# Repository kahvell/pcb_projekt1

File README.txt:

Projekt nr 1 płytki PCB w EAGLE 6.

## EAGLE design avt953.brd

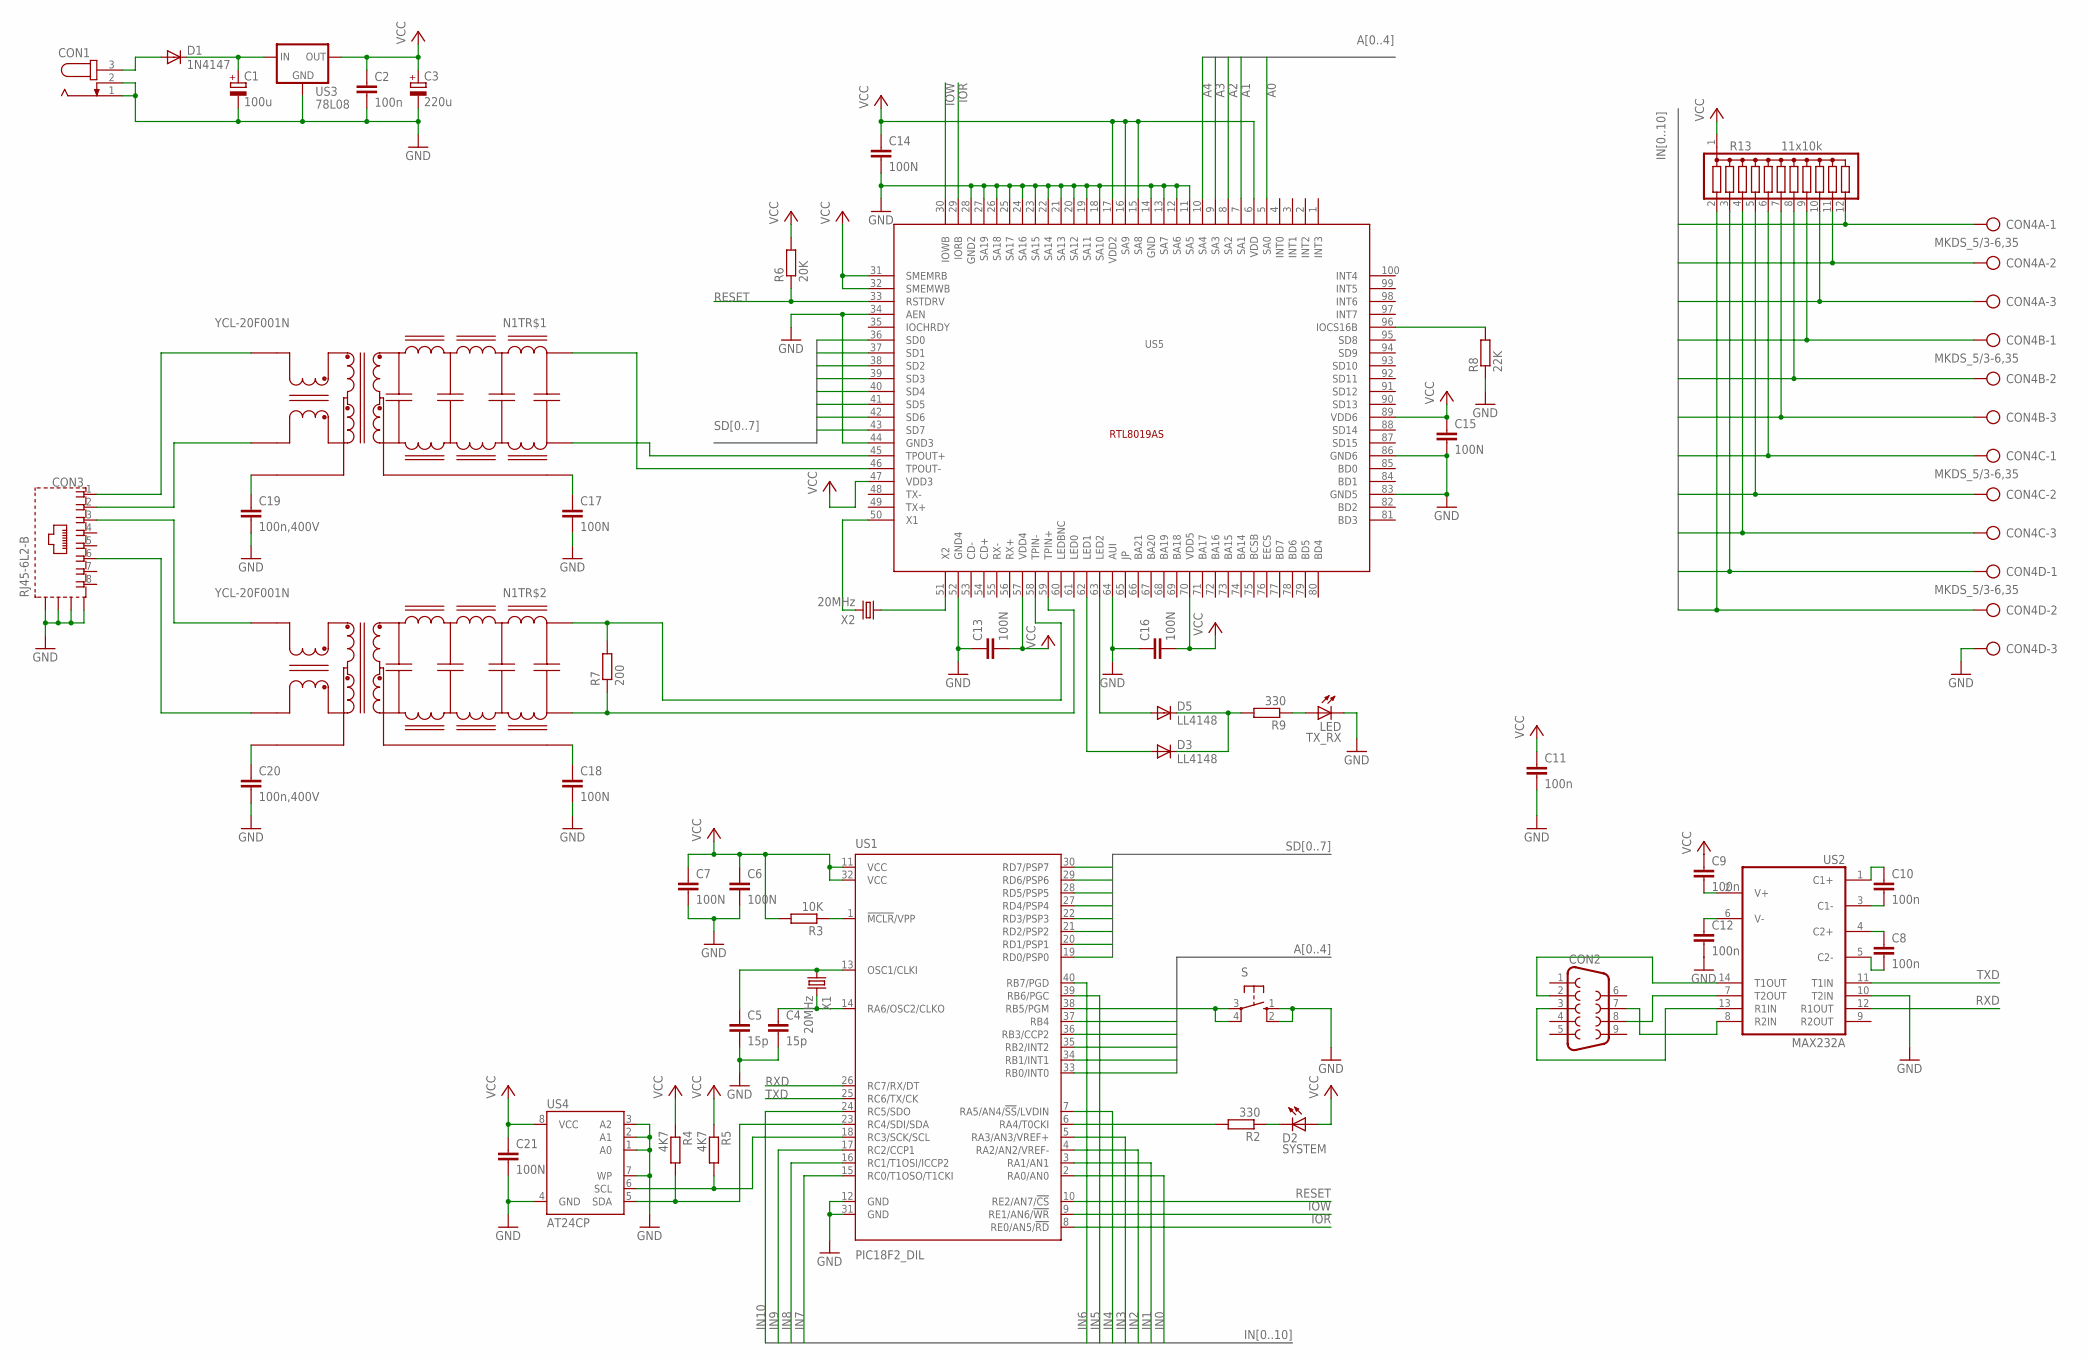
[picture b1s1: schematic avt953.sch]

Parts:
C1: 100u; TT2D5
C2, C8, C9, C10, C11, C12: 100n; C1206K
C3: 220u; TT2D5
C4, C5: 15p; C1206K
C6, C7, C13, C14, C15, C16, C17, C18, C21: 100N; C1206K
C19, C20: 100n,400V; C075-032X103
CON1: JACK-PLUG0; SPC4077
CON2: F09HP
CON3: RJ45-6L2-B; RJ45-SHIELD2
CON4A, CON4B, CON4C, CON4D: MKDS_5/3-6,35; MKDS_5/3-635
D1: 1N4147; DO35-10
D2: SYSTEM; LED5MM
D3, D5: LL4148; SOD-123_MINI-SMA
LED: TX_RX; LED5MM
N1: YCL-20F001N; DIP
R2, R9: 330; M3216
R3: 10K; M3216
R4, R5: 4K7; M3216
R6: 20K; M3216
R7: 200; M3216
R8: 22K; M3216
R13: 11x10k; SIL12
S: 10-XX; B3F-10XX
US1: PIC18F2_DIL; DIL40
US2: MAX232A; SO16L
US3: 78L08; 78XXL
US4: AT24CP; DIL08
US5: RTL8019AS
X1, X2: 20MHz; HC49/S

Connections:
A0: US1.33 (RB0/INT0), US5.5 (SA0)
A1: US1.34 (RB1/INT1), US5.7 (SA1)
A2: US1.35 (RB2/INT2), US5.8 (SA2)
A3: US1.36 (RB3/CCP2), US5.9 (SA3)
A4: US1.37 (RB4), US5.10 (SA4)
GND: C1.-, C2.2, C3.-, C4.2, C5.2, C6.2, C7.2, C11.2, C12.2, C13.1, C14.2, C15.2, C16.1, C17.2, C18.2, C19.2, C20.2, C21.2, CON1.1, CON1.2, CON2.5, CON3.S1 (S), CON3.S2 (S), CON3.S3 (S), CON3.S4 (S), CON4D.3, LED.K (C), R8.1, S.1 (S), S.2 (S1), US1.12 (GND), US1.31 (GND), US2.10 (T2IN), US2.15 (GND), US3.GND, US4.1 (A0), US4.2 (A1), US4.3 (A2), US4.4 (GND), US4.7 (WP), US5.11 (SA5), US5.12 (SA6), US5.13 (SA7), US5.14 (GND), US5.18 (SA10), US5.19 (SA11), US5.20 (SA12), US5.21 (SA13), US5.22 (SA14), US5.23 (SA15), US5.24 (SA16), US5.25 (SA17), US5.26 (SA18), US5.27 (SA19), US5.28 (GND2), US5.34 (AEN), US5.44 (GND3), US5.52 (GND4), US5.64 (AUI), US5.83 (GND5), US5.86 (GND6)
IN0: CON4A.1, R13.12, US1.2 (RA0/AN0)
IN1: CON4A.2, R13.11, US1.3 (RA1/AN1)
IN2: CON4A.3, R13.10, US1.4 (RA2/AN2/VREF-)
IN3: CON4B.1, R13.9, US1.5 (RA3/AN3/VREF+)
IN4: CON4B.2, R13.8, US1.7 (RA5/AN4/!SS!/LVDIN)
IN5: CON4B.3, R13.7, US1.39 (RB6/PGC)
IN6: CON4C.1, R13.6, US1.40 (RB7/PGD)
IN7: CON4C.2, R13.5, US1.15 (RC0/T1OSO/T1CKI)
IN8: CON4C.3, R13.4, US1.16 (RC1/T1OSI/ICCP2)
IN9: CON4D.1, R13.3, US1.17 (RC2/CCP1)
IN10: CON4D.2, R13.2, US1.24 (RC5/SDO)
IOR: US1.8 (RE0/AN5/!RD), US5.29 (IORB)
IOW: US1.9 (RE1/AN6/!WR), US5.30 (IOWB)
unnamed: C9.2, US2.2 (V+)
unnamed: C12.1, US2.6 (V-)
unnamed: C10.2, US2.3 (C1-)
unnamed: C10.1, US2.1 (C1+)
unnamed: C8.1, US2.4 (C2+)
unnamed: C8.2, US2.5 (C2-)
unnamed: CON2.2, US2.14 (T1OUT)
unnamed: CON2.8, US2.7 (T2OUT)
unnamed: CON2.3, US2.13 (R1IN)
unnamed: CON2.7, US2.8 (R2IN)
unnamed: CON1.3, D1.A
unnamed: C1.+, D1.C, US3.IN
unnamed: CON3.1, N1.P$16
unnamed: CON3.2, N1.P$14
unnamed: CON3.3, N1.P$11
unnamed: CON3.6, N1.P$9
unnamed: C19.1, N1.P$15
unnamed: C20.1, N1.P$10
unnamed: C18.1, N1.P$7
unnamed: C17.1, N1.P$2
unnamed: N1.P$3, US5.45 (TPOUT+)
unnamed: N1.P$8, R7.1, US5.59 (TPIN+)
unnamed: N1.P$1, US5.46 (TPOUT-)
unnamed: US5.50 (X1), X2.2
unnamed: N1.P$6, R7.2, US5.58 (TPIN-)
unnamed: D3.A, US5.62 (LED1)
unnamed: R8.2, US5.96 (IOCS16B)
unnamed: US5.51 (X2), X2.1
unnamed: D5.A, US5.63 (LED2)
unnamed: D3.C, D5.C, R9.2
unnamed: LED.A, R9.1
unnamed: C5.1, US1.13 (OSC1/CLKI), X1.1
unnamed: C4.1, US1.14 (RA6/OSC2/CLKO), X1.2
unnamed: R4.2, US1.23 (RC4/SDI/SDA), US4.5 (SDA)
unnamed: R3.1, US1.1 (!MCLR!/VPP)
unnamed: R2.2, US1.6 (RA4/T0CKI)
unnamed: R5.2, US1.18 (RC3/SCK/SCL), US4.6 (SCL)
unnamed: D2.K (C), R2.1
unnamed: S.3, S.4 (P1), US1.38 (RB5/PGM)
RESET: R6.1, US1.10 (RE2/AN7/!CS), US5.33 (RSTDRV)
RXD: US1.26 (RC7/RX/DT), US2.12 (R1OUT)
SD0: US1.19 (RD0/PSP0), US5.36 (SD0)
SD1: US1.20 (RD1/PSP1), US5.37 (SD1)
SD2: US1.21 (RD2/PSP2), US5.38 (SD2)
SD3: US1.22 (RD3/PSP3), US5.39 (SD3)
SD4: US1.27 (RD4/PSP4), US5.40 (SD4)
SD5: US1.28 (RD5/PSP5), US5.41 (SD5)
SD6: US1.29 (RD6/PSP6), US5.42 (SD6)
SD7: US1.30 (RD7/PSP7), US5.43 (SD7)
TXD: US1.25 (RC6/TX/CK), US2.11 (T1IN)
VCC: C2.1, C3.+, C6.1, C7.1, C9.1, C11.1, C13.2, C14.1, C15.1, C16.2, C21.1, D2.A, R3.2, R4.1, R5.1, R6.2, R13.1, US1.11 (VCC), US1.32 (VCC), US2.16 (VCC), US3.OUT, US4.8 (VCC), US5.6 (VDD), US5.15 (SA8), US5.16 (SA9), US5.17 (VDD2), US5.31 (SMEMRB), US5.32 (SMEMWB), US5.47 (VDD3), US5.57 (VDD4), US5.70 (VDD5), US5.89 (VDD6)

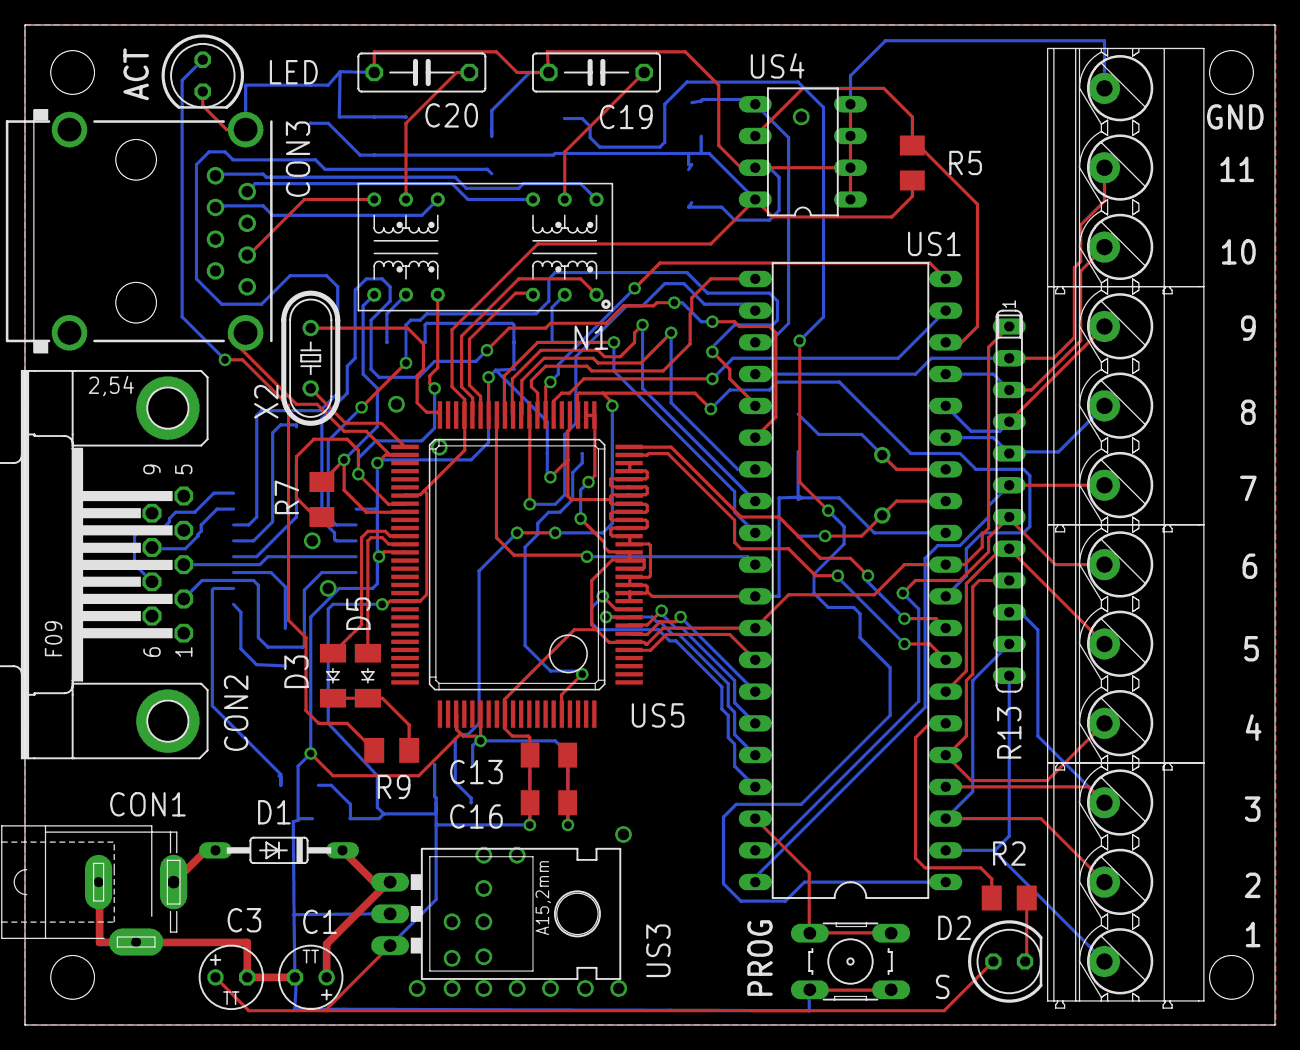
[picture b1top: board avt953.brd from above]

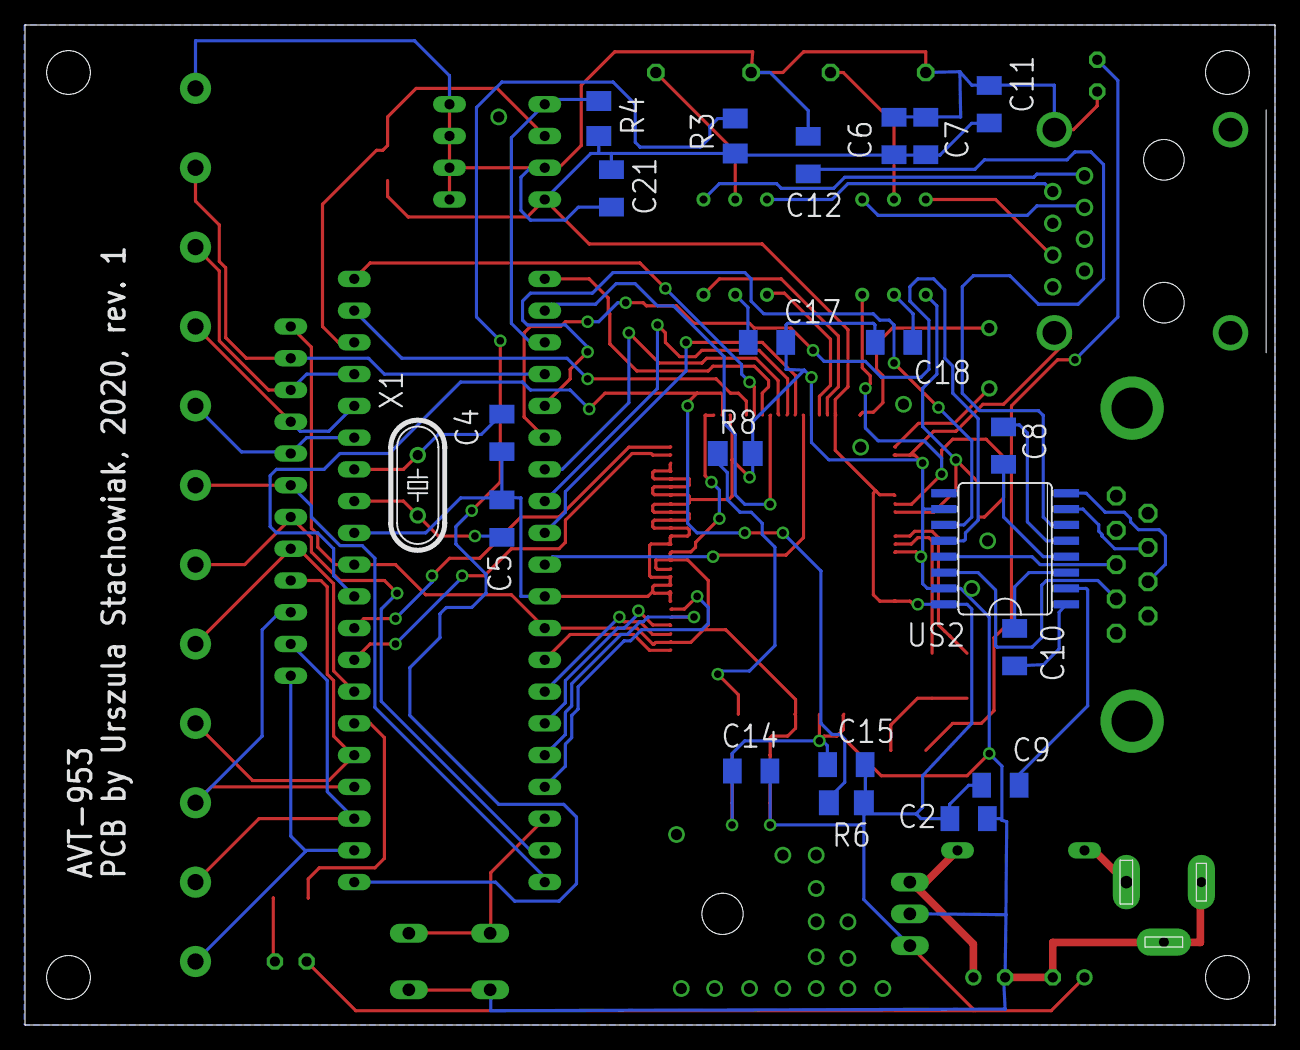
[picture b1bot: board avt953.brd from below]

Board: 2 copper layers, 100.0 x 80.0 mm, 51 parts (21 on the bottom side), 70 nets.

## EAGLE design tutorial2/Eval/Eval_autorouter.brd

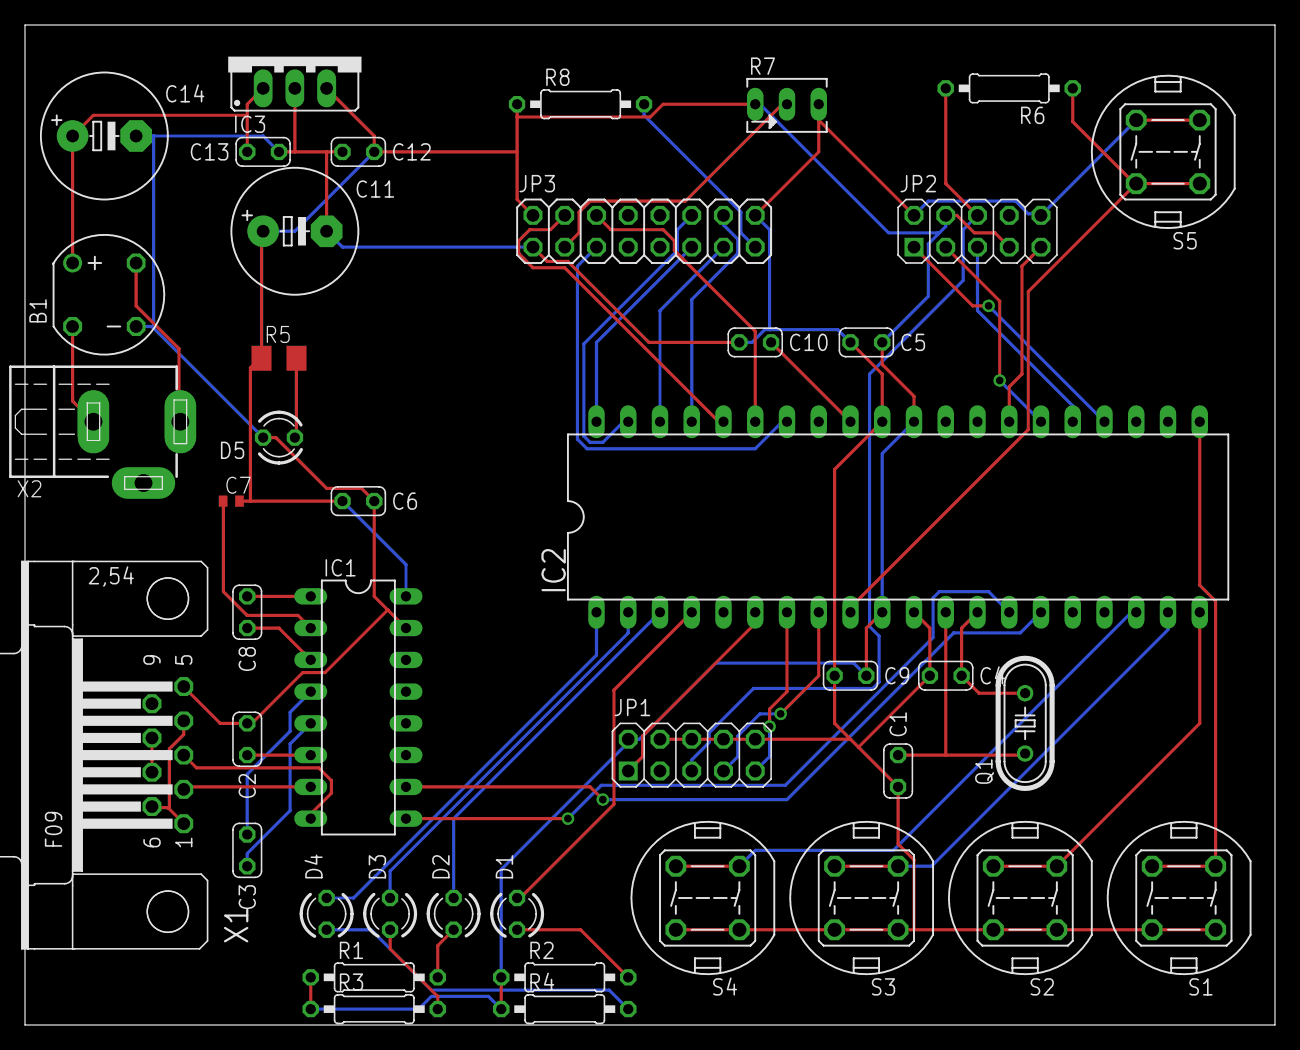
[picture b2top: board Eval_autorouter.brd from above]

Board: 2 copper layers, 100.0 x 80.0 mm, 42 parts (0 on the bottom side), 51 nets.

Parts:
B1: RB1A
C1, C4: 33pF; C025-024X044
C2, C3, C5, C6, C8, C9, C10, C12, C13: 100nF; C025-024X044
C7: 100nF; C0402
C11, C14: 470u/25V; E5-10,5
D1, D2, D3, D4: Red; LED3MM
D5: Green; LED3MM
IC1: MAX232; DIL16
IC2: MEGA16-P; DIL40
IC3: 7805; 78XXS
JP1, JP2: 2x5; 2X05
JP3: 2x8; 2X08
Q1: 16MHz; HC49/S
R1, R2, R3, R4: 220R; 0207/10@1
R5: 220R; M1206
R6: 510R; 0207/10@1
R7: 10k; B64Y
R8: 22R; 0207/10@1
S1, S2, S3, S4, S5: DTE6
X1: F09H
X2: NEB21R

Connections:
+5V: C5.2, C6.1, C7.2, C9.2, C11.+, C12.2, IC1.16, IC2.10, IC2.30, IC3.OUT, JP1.2, JP2.4, JP2.7, JP3.2, R1.1, R2.1, R3.1, R4.1, R5.1, R7.E, R8.1
/RESET: IC2.9, R6.1, S5.1, S5.2
/RESET_ISP: JP1.5, JP2.6, R6.2
DB4: IC2.40, JP3.11
DB5: IC2.39, JP3.12
DB6: IC2.38, JP3.13
DB7: IC2.37, JP3.14
E: IC2.35, JP3.6
GND: B1.-, C1.1, C2.1, C4.1, C5.1, C6.2, C9.1, C10.1, C11.-, C12.1, C13.1, C14.-, D5.K, IC1.15, IC2.11, IC2.31, IC3.GND, JP1.4, JP1.6, JP1.8, JP1.10, JP2.2, JP2.10, JP3.1, JP3.16, R7.A, S1.1, S1.2, S2.1, S2.2, S3.1, S3.2, S4.1, S4.2, S5.3, S5.4, X1.5
LED0: D4.K, IC2.1
LED1: D3.K, IC2.2
LED2: D2.K, IC2.3
LED3: D1.K, IC2.4
LED-A: JP3.15, R8.2
MISO: IC2.7, JP1.9
MOSI: IC2.6, JP1.1
unnamed: D4.A, R4.2
unnamed: D3.A, R3.2
unnamed: D2.A, R1.2
unnamed: D1.A, R2.2
unnamed: C10.2, IC2.32
unnamed: C2.2, IC1.6
unnamed: C7.1, IC1.2
unnamed: C3.2, IC1.5
unnamed: C3.1, IC1.4
unnamed: C8.2, IC1.3
unnamed: C8.1, IC1.1
unnamed: C4.2, IC2.13, Q1.2
unnamed: C1.2, IC2.12, Q1.1
unnamed: X1.1, X1.4, X1.6
unnamed: D5.A, R5.2
unnamed: B1.AC2, X2.-
unnamed: X1.7, X1.8
unnamed: B1.AC1, X2.+
unnamed: B1.+, C13.2, C14.+, IC3.IN
R/W: IC2.34, JP3.5
RS: IC2.36, JP3.4
RS232-RX0: IC1.8, X1.3
RS232-TX0: IC1.7, X1.2
RXD0: IC1.9, IC2.14
SCK: IC2.8, JP1.7
SW4: IC2.18, S4.3, S4.4
SW5: IC2.19, S3.3, S3.4
SW6: IC2.20, S2.3, S2.4
SW7: IC2.21, S1.3, S1.4
TCK: IC2.24, JP2.1
TDI: IC2.27, JP2.9
TDO: IC2.26, JP2.3
TMS: IC2.25, JP2.5
TXD0: IC1.10, IC2.15
V0: JP3.3, R7.S

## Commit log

2020-04-21 Dodano plik projektu EAGLE i specyfikację płytki do zaprojektowania.
2020-04-23 Dodano dokumentację transformatora Ethernet.
2020-04-23 Dodano dokumentację mikrokontrolera PIC.
2020-04-23 Dodano bibliotekę z układem scalonym - kontrolerem Ethernet.
2020-04-23 Dodano oryginalną biblotekę microchip.lbr z EAGLE 6.6.0.
2020-04-23 Do biblioteki microchip.lbr dodano device PIC18F452 w obudowie DIL40.
2020-04-23 Umieszczono co bardziej nietypowe komponenty na schemacie i dobrano footprinty.
2020-04-23 Dodano datasheety układów scalonych.
2020-04-23 Dodano plik .gitignore dla archiwalnych wersji płytek, schematów i bibliotek.
2020-04-23 Dopasowano nazwy na schemacie do wytycznych.
2020-04-28 Dodano firmware mikrokontrolera z projektu, zaciągnięty z archiwum Elektroniki Praktycznej.
2020-04-29 Dodano bibliotekę z transformatorem ethernetowym 10BASE-T YCL-20F001N. Umieszczono to trafo na schemacie.
2020-04-30 Zaprojektowano kompletny schemat układu.Przygotowano na jego podstawie pusty projekt płytki PCB i rozmieszczono co większe elementy.
2020-05-01 Przeprowadzono test ERC na schemacie i poprawiono zaraportowane błędy.
2020-05-01 Wstępnie rozmieszczono wszystkie elementy na projekcie płytki PCB.
2020-05-01 Dodano otwory montażowe M3 w rogach płytki.
2020-05-01 Przepuszczono płytkę przez autorouter z wynikiem 72,6%.
2020-05-01 Cofnięcie autoroutera. Zmiana kolejności wyprowadzeń IN (bo pin GND) nie był zewnętrznym pinem.
2020-05-01 Przepuszczono płytkę jeszcze raz przez autorouter, rozluźniając kryteria dodania przelotek i zmiany kierunku ścieżek. Brzydko wyszło, ale wynik 100%.
2020-05-01 Poprawki po autorouterze. Usunięto sporo przelotek, a pozostałe oddalono od siebie.
2020-05-01 Dodano szablon testu DRC za https://www.allpcb.com/standard_pcb_manufacturing_capability.html. Poddano płytkę testowi i poprawiono drobne błędy.
2020-05-01 Nie było połączenia z masą w konektorze RS232.
2020-05-01 Oblano warstwy top i bottom masą. Uzupełniono przelotki.
2020-05-01 Poprawiono i uzupełniono opisy w silkscreenie warstwy top.
2020-05-01 Poprawiono krytyczny błąd. Trzy elementy SMD na warstwie bottom nachodziły na siebie.
2020-05-01 Uzupełniono silkscreen na warstwie bottom.
2020-05-01 Włączono wyświetlanie wszystkich standardowych warstw.
2020-05-01 Zmaiana nazwy jednego z plików dla zachowania spójności.
2020-05-01 Dodano pliki gerber zgodnie z wytycznymi allpcb.com
2020-05-01 Dodano wydruki poszczególnych warstw do produkcji płytek metodą żelazkową.
2020-05-02 Przeniesiono projekt do podfolderu na... projekt.
2020-05-02 Dodano rozwiązania z trzech części tutoriala.
